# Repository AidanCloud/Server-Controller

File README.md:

# Server-Controller
A macropad designed to control the status of a Raspberry Pi server without having to plug in a monitor. I has three buttons and a small screen to display status updates.

BOM: 
- 1 XIAO RP2040
- 1 SSD1306 OLED Display
- 3 Cherry MX Switches
- 3 Blank DSA Keycaps
- 4 M3x16 Bolts
- 4 M3 Heatsets

Schematic            |  PCB         |   Case
:-------------------------:|:-------------------------:|:-------------------------:|
   |    |

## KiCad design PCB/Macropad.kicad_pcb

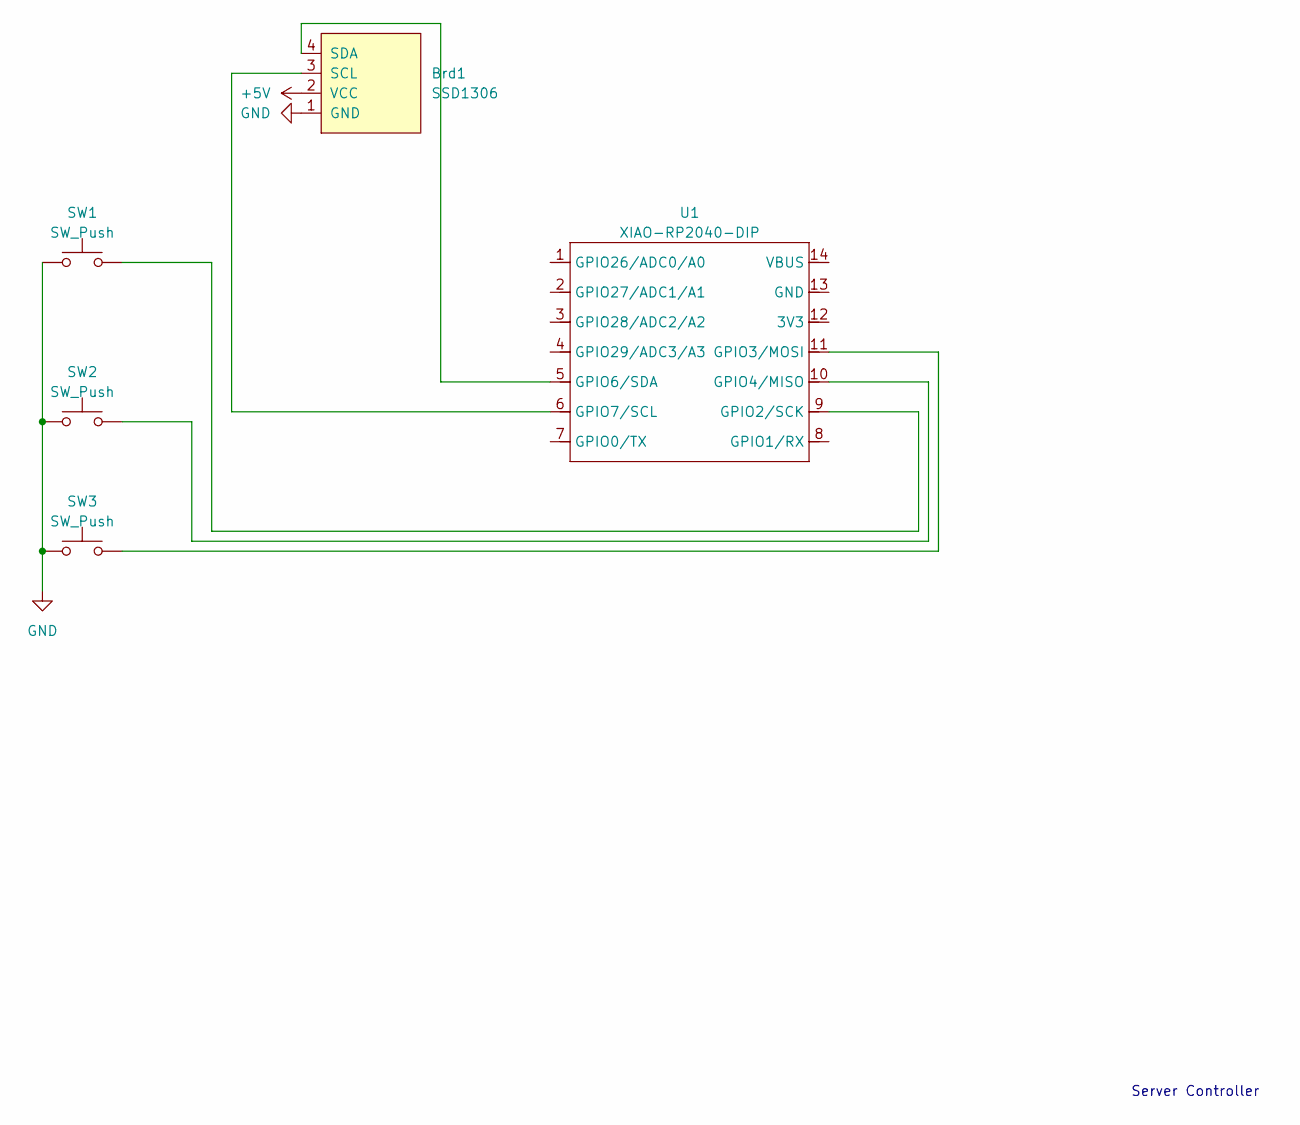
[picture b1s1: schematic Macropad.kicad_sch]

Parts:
Brd1: SSD1306; 128x64OLED
SW1, SW2, SW3: SW_Push; SW_Cherry_MX_1.00u_PCB
U1: XIAO-RP2040-DIP

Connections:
+5V: Brd1.2 (VCC)
GND: Brd1.1 (GND), SW1.1, SW2.1, SW3.2
unnamed: Brd1.3 (SCL), U1.6 (GPIO7/SCL)
unnamed: Brd1.4 (SDA), U1.5 (GPIO6/SDA)
unnamed: SW1.2, U1.9 (GPIO2/SCK)
unnamed: SW3.1, U1.11 (GPIO3/MOSI)
unnamed: SW2.2, U1.10 (GPIO4/MISO)

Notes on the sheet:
Server Controller

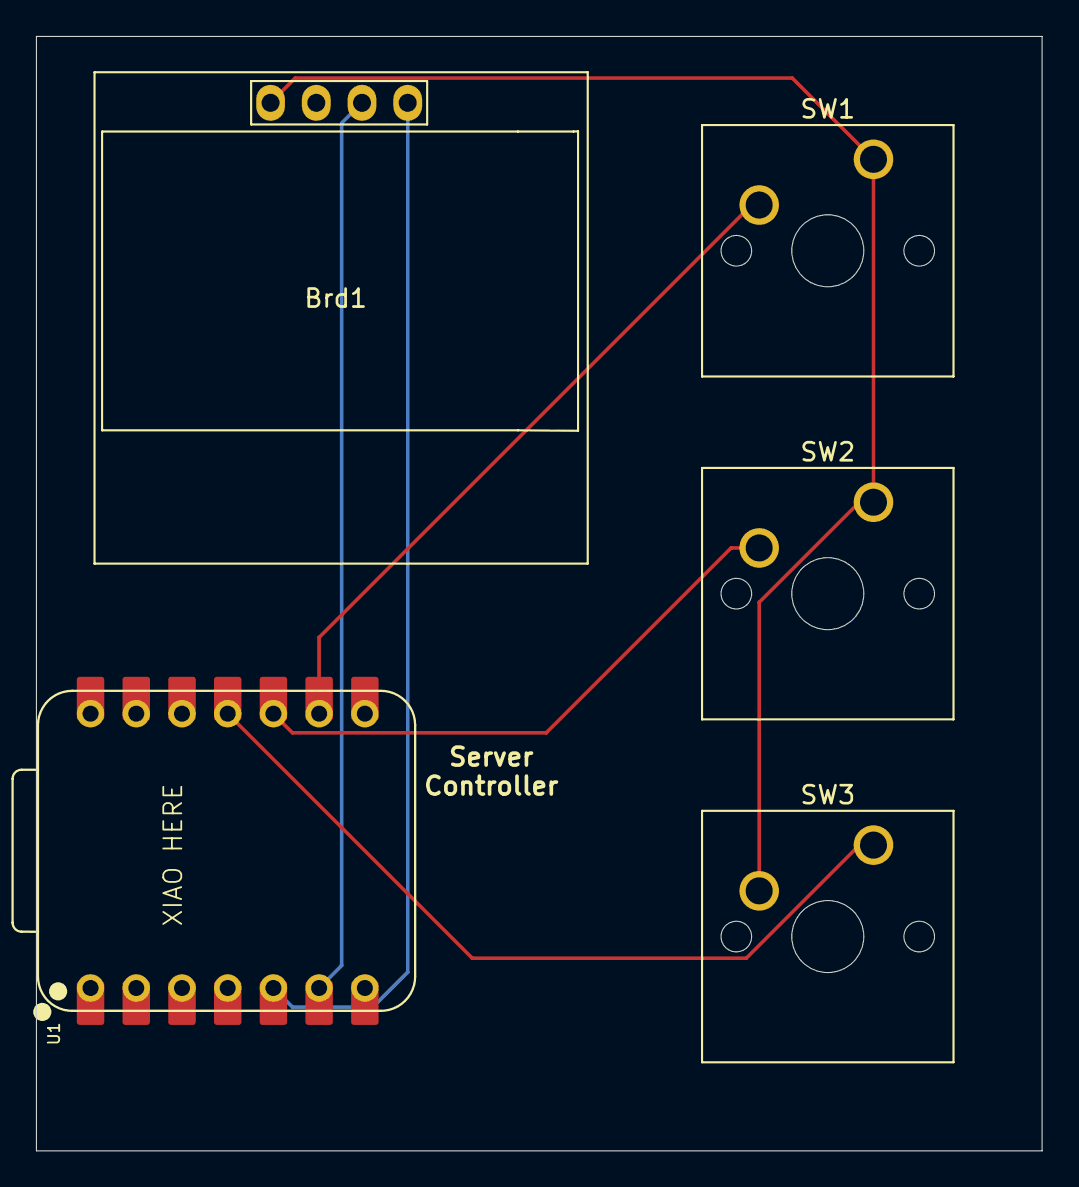
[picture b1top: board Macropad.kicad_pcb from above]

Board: 2 copper layers, 55.9 x 61.9 mm, 5 parts (0 on the bottom side), 6 nets.
